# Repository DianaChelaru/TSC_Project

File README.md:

Acest proiect îmbină mai multe componente electronice conectate la un microcontroler ESP32-C6-WROOM-1-N8, creând o platformă embedded compactă destinată aplicațiilor cu senzoristică, comunicație wireless și o interfață de utilizator minimală. Platforma poate gestiona o serie de funcționalități, inclusiv monitorizarea și interacțiunea cu date în timp real, gestionarea energiei și stocarea datelor.

    Bill of Materials
|Componenta	|Link|	Datasheet|
|-----------|-----------------|---------------|
|112A-TAAR-R03_ATTEND |	https://store.comet.bg/en/Catalogue/Product/43497/ |	https://store.comet.bg/en/Catalogue/Product/43497/ |
|744043680IND_4828-WE-TPC_WRE |	https://www.digikey.sg/en/models/1638515 |	https://www.we-online.com/components/products/datasheet/744043680.pdf |
|ADAFRUIT_LEDCHIP-LED0603 |	https://www.snapeda.com/parts/KP-1608SURCK/Kingbright/view-part/?ref=search&t=LED%200603 |	https://www.snapeda.com/parts/KP-1608SURCK/Kingbright/datasheet/ |  
|SAMACSYS_PARTS_USB4110-GF-A|	https://componentsearchengine.com/part-view/USB4110-GF-A/GCT%20(GLOBAL%20CONNECTOR%20TECHNOLOGY) |	https://gct.co/files/drawings/usb4110.pdf |
|BD5229G-TR|	https://componentsearchengine.com/part-view/BD5229G-TR/ROHM%20Semiconductor |	https://datasheet.datasheetarchive.com/originals/distributors/Datasheets_SAMA/f2b9741ef86007909f138d561a359946.pdf |
|CPH3225A|	https://www.snapeda.com/parts/CPH3225A/Seiko+Instruments/view-part/?ref=eda |	https://www.snapeda.com/parts/CPH3225A/Seiko%20Instruments/datasheet/ |
|QWIIC_CONNECTORJS-1MM|	https://www.snapeda.com/parts/PRT-14417/SparkFun/view-part/ |	https://www.snapeda.com/parts/PRT-14417/SparkFun%20Electronics/datasheet/ |
|BUTTON_CUSYOMV1|	https://industry.panasonic.com/global/en/downloads?tab=cad&small_g_cd=203&part_no=EVQPUJ02K&q=RVZRUFVKMDJLJTdDMTMlN0MyMDMlN0MzNDU5JTdDMSU3QyU3QyU3Q2ZhbHNl	| https://industry.panasonic.com/global/en/downloads?tab=catalog&small_g_cd=203&part_no=EVQPUJ02K&q=RVZRUFVKMDJLJTdDMTMlN0MyMDMlN0MzNDU5JTdDMSU3QyU3QzIlN0NmYWxzZQ%3D%3D |
|ESP32_WROVER_EAGLE-LTSPICE_CC0402|	https://componentsearchengine.com/part-view/CC0402MRX5R5BB106/YAGEO |	https://componentsearchengine.com/Datasheets/2/CC0402MRX5R5BB106.pdf |
|CPH3225A|	https://www.snapeda.com/parts/CPH3225A/Seiko+Instruments/view-part/?ref=eda |	https://www.snapeda.com/parts/CPH3225A/Seiko%20Instruments/datasheet/ |
|DS3231SN|	https://www.snapeda.com/parts/DS3231SN%23/Analog+Devices/view-part/?ref=eda |	https://www.snapeda.com/parts/DS3231SN%23/Analog%20Devices/datasheet/ |
|ESP32_WROVER_EAGLE-LTSPICE_RR0402|	https://www.snapeda.com/parts/RC0402FR-07226RL/Yageo/view-part/	| https://www.snapeda.com/parts/RC0402FR-07226RL/Yageo/datasheet/ |
|ESP32_WROVER_BME680_BME680|	https://www.snapeda.com/parts/BME680/Bosch/view-part/?welcome=home |	https://www.snapeda.com/parts/BME680/Bosch%20Sensortec/datasheet/ |
|ESP32_WROVER_EAGLE-LTSPICE_CC0402|	https://componentsearchengine.com/Datasheets/2/CC0402MRX5R5BB106.pdf |	https://componentsearchengine.com/part-view/CC0402MRX5R5BB106/YAGEO |
|ESP32_WROVER_SPARKFUN-DISCRETESEMI_MOSFET_PCH-DMG2305UX-7|	https://componentsearchengine.com/part-view/DMG2305UX-7/Diodes%20Incorporated |	https://www.diodes.com//assets/Datasheets/DMG2305UX.pdf |
|ESP32C6_VARISTORCN1812|	https://www.mouser.co.uk/ProductDetail/EPCOS-TDK/B72520T0350K062?qs=dEfas%2FXlABIszF52uu7vrg%3D%3D	| https://www.tdk-electronics.tdk.com/inf/75/db/CTVS_14/Surge_protection_series.pdf |
|ESP32-C6-WROOM-1-N8| 	https://www.snapeda.com/parts/ESP32-C6-WROOM-1-N8/Espressif+Systems/view-part/?ref=eda |	https://www.snapeda.com/parts/ESP32-C6-WROOM-1-N8/Espressif%20Systems/datasheet/ |
|FH34SRJ-24S-0.5SH_99_ |	https://componentsearchengine.com/part-view/XC6220A331MR-G/Torex	| https://product.torexsemi.com/system/files/series/xc6220.pdf |
|MAX17048G+T10|	https://www.snapeda.com/parts/MAX17048G+T10/Analog+Devices/view-part/?ref=eda |	https://www.snapeda.com/parts/MAX17048G+T10/Analog%20Devices/datasheet/ |
|MBR0530|	https://ro.mouser.com/ProductDetail/KYOCERA-AVX/SD0805S020S1R0?qs=jCA%252BPfw4LHbpkAoSnwrdjw%3D%3D |	https://ro.mouser.com/datasheet/2/40/schottky-3165252.pdf |
|PGB1010603MR|	https://www.snapeda.com/parts/PGB1010603MR/Littelfuse/view-part/?ref=eda |	https://www.snapeda.com/parts/PGB1010603MR/Littelfuse%20Inc./datasheet/ |
|MCP73831 |	https://www.digikey.com/en/models/1874108 |	https://ww1.microchip.com/downloads/aemDocuments/documents/APID/ProductDocuments/DataSheets/MCP73831-Family-Data-Sheet-DS20001984H.pdf |
|RCL_CPOL-EUCT3528|	https://ro.mouser.com/ProductDetail/Vishay-Sprague/TR3B106K025C1300?qs=jCGqFXxTmLdffnuDkXzk1g%3D%3D |	https://www.vishay.com/docs/40080/tr3.pdf |
|SI1308EDL-T1-GE3|	https://componentsearchengine.com/part-view/SI1308EDL-T1-GE3/Vishay	| https://componentsearchengine.com/Datasheets/1/SI1308EDL-T1-GE3.pdf |
| SJ |	https://grabcad.com/library/solder-jumpers-1 | 
|USBLC6-2SC6Y |	https://www.snapeda.com/parts/USBLC6-2SC6Y/STMicroelectronics/view-part/?ref=eda	| https://www.snapeda.com/parts/USBLC6-2SC6Y/STMicroelectronics/datasheet/ |
|W25Q512JVEIQ|	https://www.snapeda.com/parts/W25Q512JVEIQ/Winbond+Electronics/view-part/?ref=eda |	https://www.snapeda.com/parts/W25Q512JVEIQ/Winbond%20Electronics/datasheet/ |
|XC6220A331MR-G|	https://componentsearchengine.com/part-view/XC6220A331MR-G/Torex |	https://product.torexsemi.com/system/files/series/xc6220.pdf|

    1. Microcontrolerul ESP32-C6-WROOM-1-N8
Descriere: Acesta este nucleul sistemului nostru și va gestiona toată logica și comunicațiile. Este un microcontroler cu suport pentru Wi-Fi și Bluetooth Low Energy (BLE), având o capacitate de procesare ridicată și multiple periferice integrate.

Componente hardware conectate:

Pinout: Conectarea senzorilor și modulelor va depinde de alegerea pinilor pe care i-am selectat pe ESP32, detaliată în documentație.

Interfețe: ESP32 folosește interfețe precum I2C, SPI și UART pentru a comunica cu componentele periferice.

    2. Senzori
Senzor de temperatură și umiditate (ex. DHT22):

Interfață: Digitală

Rol: Măsurarea temperaturii și umidității în mediu.

Comunicare: Acesta va comunica cu ESP32 folosind pinul GPIO (general-purpose input/output) pentru a obține valorile măsurate.

Senzor de lumină (ex. LDR):

Interfață: Analogică

Rol: Măsurarea intensității luminii din mediu.

Comunicare: Va fi conectat la un pin analogic al ESP32 pentru a permite citirea valorilor de lumină.

    3. RTC (Real-Time Clock)
Componente: Modul RTC (de exemplu, DS3231)

Interfață: I2C

Rol: Ținerea orei și datei, chiar și când microcontrolerul este alimentat cu baterie.

Comunicare: ESP32 se va conecta la RTC prin interfața I2C. Datele și ora vor fi extrase periodic din RTC pentru a menține sincronizarea corectă a sistemului.

    4. Memorie Externă
Componente: Modul de memorie flash (ex. SPI Flash)

Interfață: SPI

Rol: Stocarea datelor de configurare, date temporare, sau orice altă informație care trebuie păstrată între restarturi ale sistemului.

Comunicare: Memoria externă va comunica cu ESP32 prin interfața SPI, permițând citirea și scrierea rapidă a datelor.

    5. Alimentare și Managementul Energiei
Componente:

Regulator de tensiune: Acesta va asigura alimentarea stabilă a întregului sistem.

Baterie Li-Ion: O baterie de 3.7V va fi utilizată pentru a alimenta sistemul într-un mod eficient.

Consumul de Energie:

ESP32 este un microcontroler cu consum variabil, dar în mod normal consumă aproximativ 160 mA în mod activ și mult mai puțin în modul de adormire. Prin gestionarea corectă a modurilor de adormire, se poate reduce consumul total de energie la un nivel foarte scăzut.

Optimizare: Implementarea unui algoritm de gestionare a energiei va permite microcontrolerului să intre în moduri de adormire adâncă în timpul perioadelor de inactivitate, economisind astfel energie.

    6. Interfețe de Comunicație
Wi-Fi (IEEE 802.11b/g/n): ESP32 va fi capabil să comunice prin rețele Wi-Fi pentru a trimite date la servere sau pentru a se conecta la alte dispozitive.

Bluetooth Low Energy (BLE): Pentru comunicații cu alte dispozitive Bluetooth, cum ar fi smartphone-uri sau alte sisteme integrate.

    7. Protecții și Siguranță
Protecție la supratensiune și supracurent: Sistemul va include diode și rezistențe de protecție pentru a preveni daunele cauzate de condiții de tensiune necontrolată.

Siguranța bateriei: Managementul bateriei va include circuite de protecție pentru a preveni supraîncărcarea sau descărcarea excesivă.

    ⚡ Calcule de consum
Acestea sunt estimările de consum pentru fiecare componentă principală a platformei:

ESP32-C6 în modul activ: Aproximativ 80 mA.

Senzori activi (maxim): Între 10-20 mA.

În modul standby: Sub 10 mA, cu ESP în deep sleep și senzorii inactivi.

MCP73831 (încărcare): Până la 500 mA, în funcție de configurare.

Consum optimizat:

LDO XC6220A331MR-G, care este eficient la sarcini joase.

Mod de deep sleep al ESP32-C6 între măsurători.

Control MOSFET pentru a alimenta perifericele doar când este necesar.

    🔌 Pini folosiți pe ESP32-C6
Acestea sunt conexiunile pinilor ESP32-C6 la diversele componente ale proiectului:

|Pin ESP32-C6 |	Funcție	  |   Conectat la|
|-----------|--------------|-------------|  
|GPIO0   	  |  Buton USER	|    BUTTON_CUSTOMV1|
|GPIO1 (TX)  |	UART TX	     |   USB4110-GF-A|
|GPIO2 (RX)	 |   UART RX	  |      USB4110-GF-A|
|GPIO3	       | SDA I2C	  |      BME680, DS3231, MAX17048|
|GPIO4	      |  SCL I2C	  |      BME680, DS3231, MAX17048|
|GPIO5	       | SPI CS	      |  W25Q512JVEIQ|
|GPIO6	      |  SPI CLK	  |      W25Q512JVEIQ|
|GPIO7	      |  SPI MISO	  |  W25Q512JVEIQ|
|GPIO8	      |  SPI MOSI	  |  W25Q512JVEIQ|
|GPIO9	      |  LED	      |      ADAFRUIT_LEDCHIP-LED0603|
|GPIO10	      |  MOSFET control |	SI1308EDL-T1-GE3|

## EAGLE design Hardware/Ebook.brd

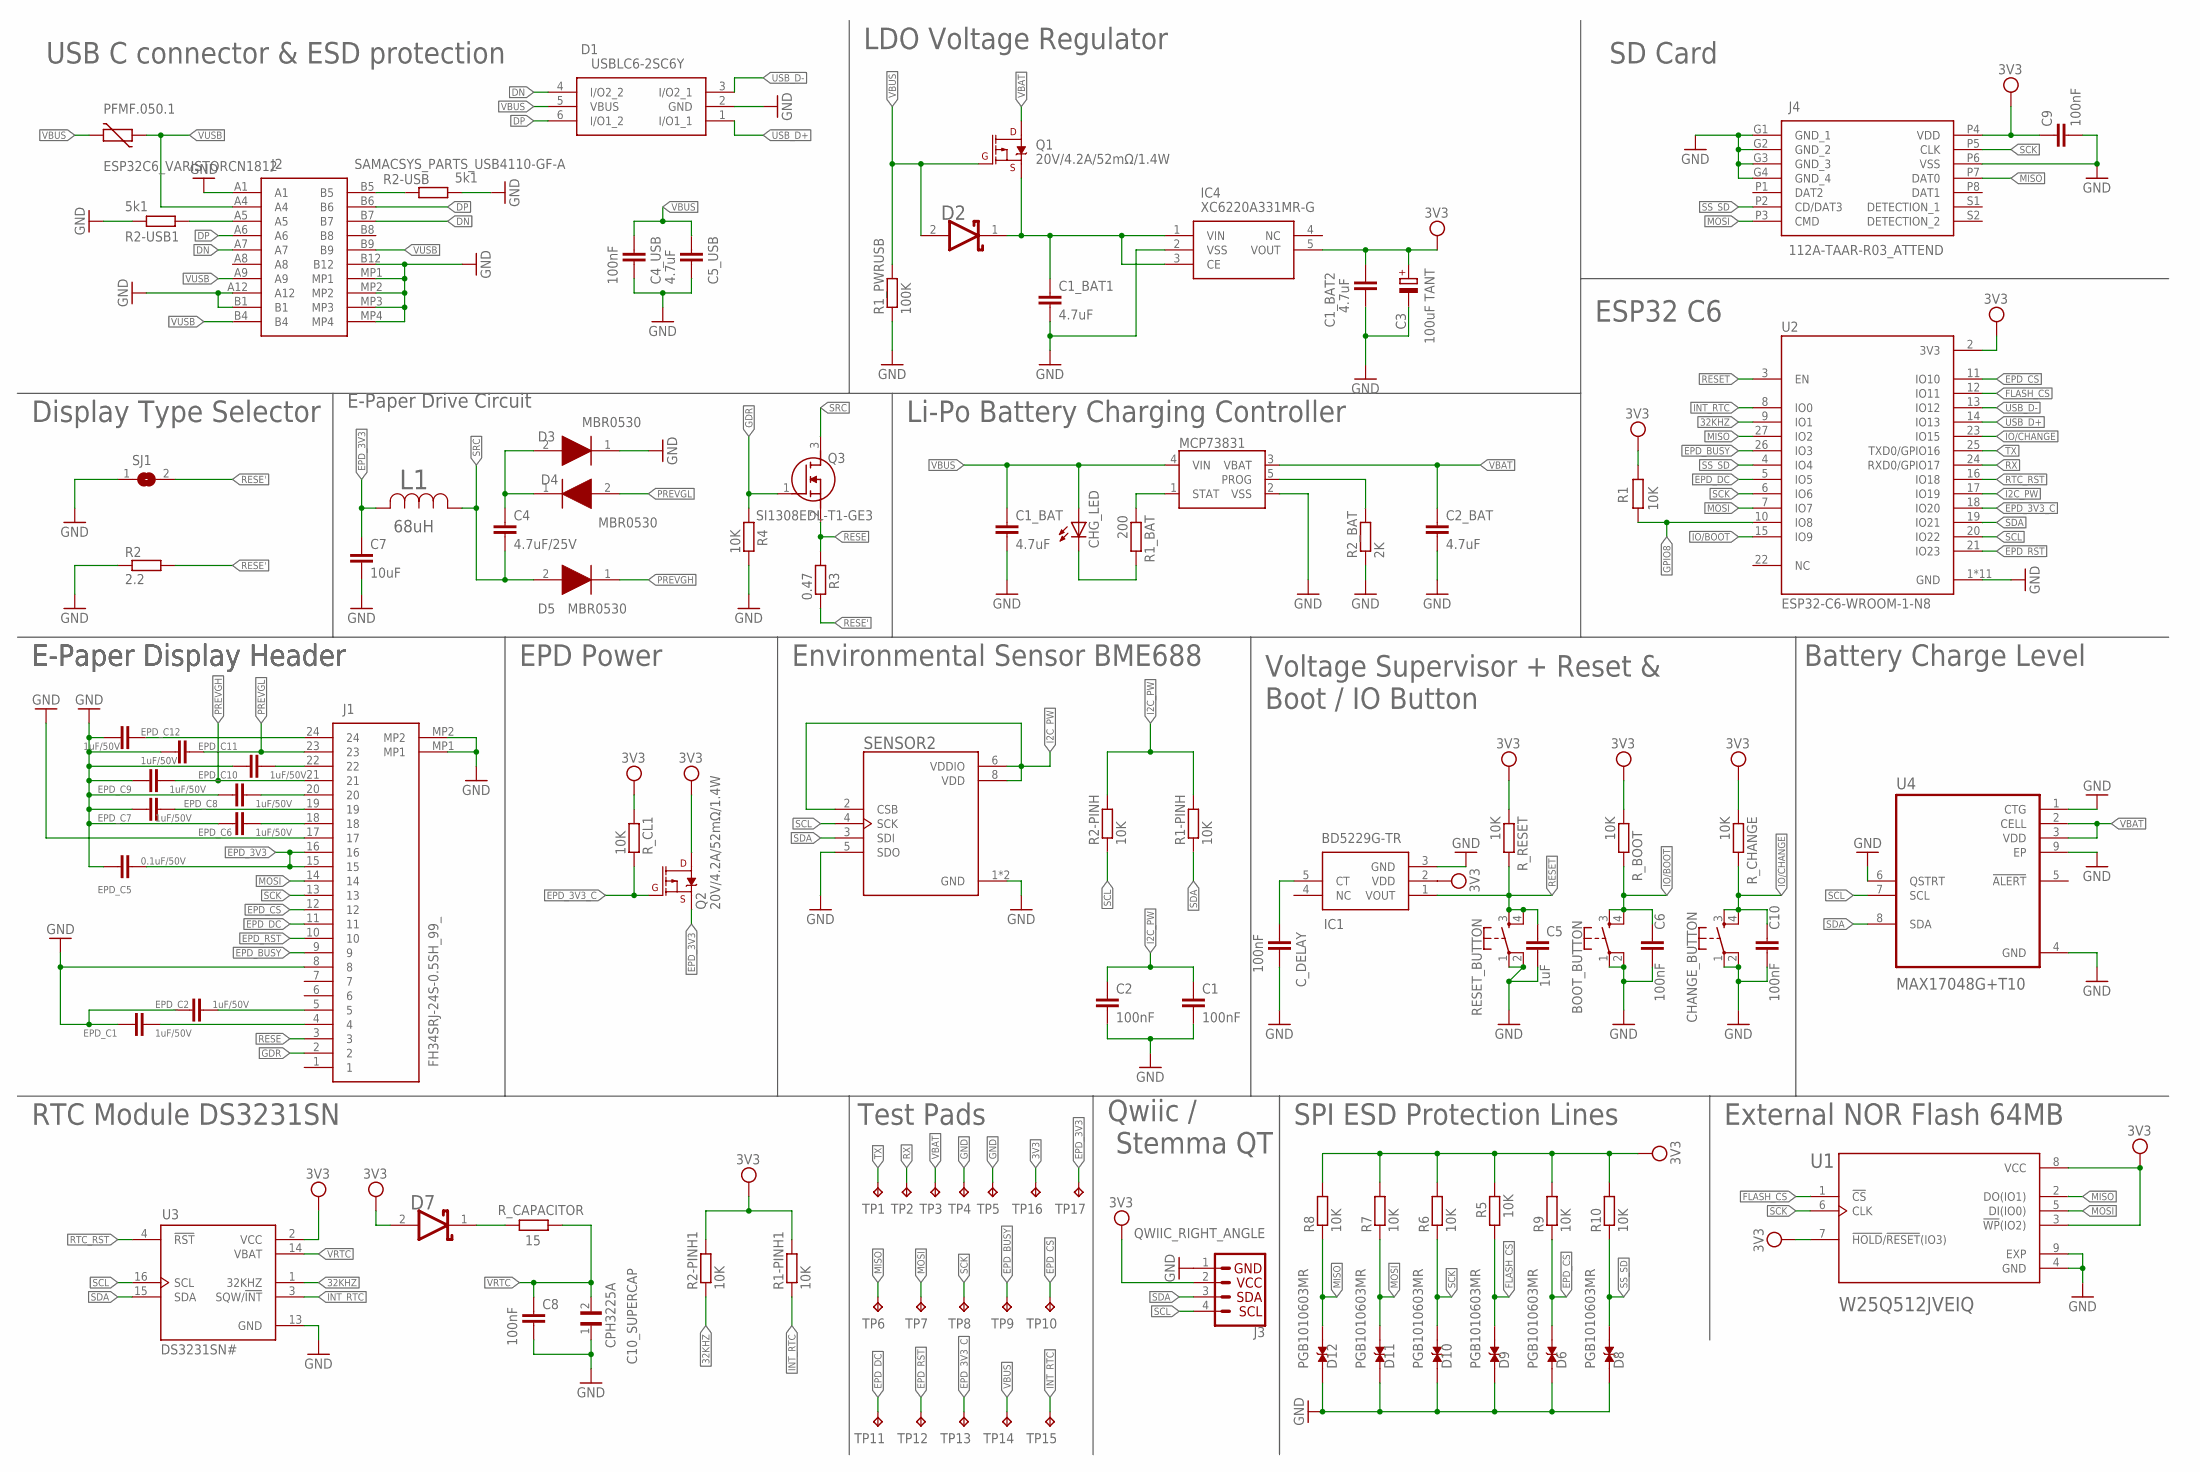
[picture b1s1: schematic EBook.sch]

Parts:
BOOT_BUTTON: BUTTON_CUSYOMV1; MYBUTTON
C1, C2, C4_USB, C6, C8, C9, C10: 100nF; EAGLE-LTSPICE_C0402
C1_BAT, C1_BAT1, C1_BAT2, C2_BAT, C5_USB: 4.7uF; EAGLE-LTSPICE_C0402
C3: 100uF TANT; RCL_CT3528
C4: 4.7uF/25V; EAGLE-LTSPICE_C0402
C5: 1uF; EAGLE-LTSPICE_C0402
C7: 10uF; EAGLE-LTSPICE_C0402
C10_SUPERCAP: CPH3225A; CAPCP3225X100N
CHANGE_BUTTON: BUTTON_CUSYOMV1; MYBUTTON
CHG_LED: ADAFRUIT_LEDCHIP-LED0603; ADAFRUIT_CHIP-LED0603
C_DELAY: 100nF; EAGLE-LTSPICE_C0402
D1: USBLC6-2SC6Y; SOT95P280X145-6N
D2, D7: ESP32_WROVER_AVX---SD0805S020S1R0_AVX_SD0805S020S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; ESP32_WROVER_AVX---SD0805S020S1R0_AVX_SD0805S020S1R0_0
D3, D4, D5: MBR0530; SOD3716X135N
D6, D8, D9, D10, D11, D12: PGB1010603MR; DIOC1608X36N
EPD_C1, EPD_C2, EPD_C6, EPD_C7, EPD_C8, EPD_C9, EPD_C10, EPD_C11, EPD_C12: 1uF/50V; EAGLE-LTSPICE_C0402
EPD_C5: 0.1uF/50V; EAGLE-LTSPICE_C0402
IC1: BD5229G-TR; SOT95P280X125-5N
IC4: XC6220A331MR-G; SOT95P280X120-5N
J1: FH34SRJ-24S-0.5SH_99_; FH34SRJ24S05SH99
J2: SAMACSYS_PARTS_USB4110-GF-A; SAMACSYS_PARTS_USB4110GFA
J3: QWIIC_RIGHT_ANGLE; JST04_1MM_RA
J4: 112A-TAAR-R03_ATTEND; 112ATAARR03ATTEND
L1: 68uH; IND_4828-WE-TPC_WRE
MCP73831: ESP32_WROVER_SPARKFUN-IC-POWER_MCP73831; ESP32_WROVER_SPARKFUN-IC-POWER_SOT23-5
PFMF.050.1: ESP32C6_VARISTORCN1812; ESP32C6_VARISTOR_CT/CN1812
Q1, Q2: 20V/4.2A/52mΩ/1.4W; ESP32_WROVER_SPARKFUN-DISCRETESEMI_SOT23-3
Q3: SI1308EDL-T1-GE3; SOT65P210X110-3N
R1, R1-PINH, R1-PINH1, R2-PINH, R2-PINH1, R4, R5, R6, R7, R8, R9, R10: 10K; ESP32_WROVER_EAGLE-LTSPICE_R0402
R1_BAT: 200; ESP32_WROVER_EAGLE-LTSPICE_R0402
R1_PWRUSB: 100K; ESP32_WROVER_EAGLE-LTSPICE_R0402
R2: 2.2; ESP32_WROVER_EAGLE-LTSPICE_R0402
R2-USB, R2-USB1: 5k1; ESP32_WROVER_EAGLE-LTSPICE_R0402
R2_BAT: 2K; ESP32_WROVER_EAGLE-LTSPICE_R0402
R3: 0.47; ESP32_WROVER_EAGLE-LTSPICE_R0402
RESET_BUTTON: BUTTON_CUSYOMV1; MYBUTTON
R_BOOT: 10K; ESP32_WROVER_EAGLE-LTSPICE_R0402
R_CAPACITOR: 15; ESP32_WROVER_EAGLE-LTSPICE_R0402
R_CHANGE: 10K; ESP32_WROVER_EAGLE-LTSPICE_R0402
R_CL1: 10K; ESP32_WROVER_EAGLE-LTSPICE_R0402
R_RESET: 10K; ESP32_WROVER_EAGLE-LTSPICE_R0402
SENSOR2: ESP32_WROVER_BME680_BME680; ESP32_WROVER_BME680_PSON80P300X300X100-8N
SJ1: SJ
TP1, TP2, TP3, TP4, TP5, TP6, TP7, TP8, TP9, TP10, TP11, TP12, TP13, TP14, TP15, TP16, TP17: TPTP20R; TP20R
U1: W25Q512JVEIQ; SON127P600X800X80-9N
U2: ESP32-C6-WROOM-1-N8; XCVR_ESP32-C6-WROOM-1-N8
U3: DS3231SN#; SOIC127P1032X265-16N
U4: MAX17048G+T10; SON50P200X200X80-9N

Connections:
3V3: C1_BAT2.1, C3.+, C9.1, D7.2 (ANODE), IC1.2 (VDD), IC4.5 (VOUT), J3.2, J4.P4 (VDD), Q2.3 (D), R1.1, R1-PINH1.2, R2-PINH1.2, R5.2, R6.2, R7.2, R8.2, R9.2, R10.2, R_BOOT.1, R_CHANGE.1, R_CL1.1, R_RESET.1, TP16.TP, U1.3 (!WP!(IO2)), U1.7 (!HOLD!/!RESET!(IO3)), U1.8 (VCC), U2.2 (3V3), U3.2 (VCC)
32KHZ: R2-PINH1.1, U2.9 (IO1), U3.1 (32KHZ)
DN: D1.4 (I/O2_2), J2.A7, J2.B7
DP: D1.6 (I/O1_2), J2.A6, J2.B6
EPD_3V3: C7.1, EPD_C5.1, J1.15, J1.16, L1.2, Q2.2 (S), TP17.TP
EPD_3V3_C: Q2.1 (G), R_CL1.2, TP13.TP, U2.18 (IO20)
EPD_BUSY: J1.9, TP9.TP, U2.26 (IO3)
EPD_CS: D6.2, J1.12, R9.1, TP10.TP, U2.11 (IO10)
EPD_DC: J1.11, TP11.TP, U2.5 (IO5)
EPD_RST: J1.10, TP12.TP, U2.21 (IO23)
FLASH_CS: D9.2, R5.1, U1.1 (!CS), U2.12 (IO11)
GDR: J1.2, Q3.1 (G), R4.1
GND: BOOT_BUTTON.1, BOOT_BUTTON.2, C1.2, C1_BAT.2, C1_BAT1.2, C1_BAT2.2, C2.2, C2_BAT.2, C3.-, C4_USB.2, C5.2, C5_USB.2, C6.2, C7.2, C8.2, C9.2, C10.2, C10_SUPERCAP.1, CHANGE_BUTTON.1, CHANGE_BUTTON.2, C_DELAY.2, D1.2 (GND), D3.1 (K), D6.1, D8.1, D9.1, D10.1, D11.1, D12.1, EPD_C1.2, EPD_C2.2, EPD_C5.2, EPD_C6.2, EPD_C7.2, EPD_C8.2, EPD_C9.2, EPD_C10.2, EPD_C11.2, EPD_C12.2, IC1.3 (GND), IC4.2 (VSS), J1.8, J1.17, J1.MP1, J1.MP2, J2.A1, J2.A12, J2.B1, J2.B12, J2.MP1, J2.MP2, J2.MP3, J2.MP4, J3.1, J4.G1 (GND_1), J4.G2 (GND_2), J4.G3 (GND_3), J4.G4 (GND_4), J4.P6 (VSS), MCP73831.2 (VSS), R1_PWRUSB.1, R2.1, R2-USB.2, R2-USB1.1, R2_BAT.1, R4.2, RESET_BUTTON.1, RESET_BUTTON.2, SENSOR2.1 (GND), SENSOR2.5 (SDO), SENSOR2.7 (GND), SJ1.1, TP4.TP, TP5.TP, U1.4 (GND), U1.9 (EXP), U2.1 (GND), U2.28 (GND), U2.29_1 (GND), U2.29_2 (GND), U2.29_3 (GND), U2.29_4 (GND), U2.29_5 (GND), U2.29_6 (GND), U2.29_7 (GND), U2.29_8 (GND), U2.29_9 (GND), U3.13 (GND), U4.1 (CTG), U4.4 (GND), U4.6 (QSTRT), U4.9 (EP)
GPIO8: R1.2, U2.10 (IO8)
I2C_PW: C1.1, C2.1, R1-PINH.2, R2-PINH.2, SENSOR2.2 (CSB), SENSOR2.6 (VDDIO), SENSOR2.8 (VDD), U2.17 (IO19)
INT_RTC: R1-PINH1.1, TP15.TP, U2.8 (IO0), U3.3 (SQW/!INT)
IO/BOOT: BOOT_BUTTON.3, BOOT_BUTTON.4, C6.1, R_BOOT.2, U2.15 (IO9)
IO/CHANGE: C10.1, CHANGE_BUTTON.3, CHANGE_BUTTON.4, R_CHANGE.2, U2.23 (IO15)
MISO: D12.2, J4.P7 (DAT0), R8.1, TP6.TP, U1.2 (DO(IO1)), U2.27 (IO2)
MOSI: D11.2, J1.14, J4.P3 (CMD), R7.1, TP7.TP, U1.5 (DI(IO0)), U2.7 (IO7)
unnamed: J2.B5, R2-USB.1
unnamed: EPD_C6.1, J1.18
unnamed: J2.A5, R2-USB1.2
unnamed: C1_BAT1.1, D2.1 (CATHODE), IC4.1 (VIN), IC4.3 (CE), Q1.2 (S)
unnamed: C4.1, D3.2 (A), D4.1 (K)
unnamed: EPD_C7.1, J1.19
unnamed: MCP73831.5 (PROG), R2_BAT.2
unnamed: MCP73831.1 (STAT), R1_BAT.1
unnamed: CHG_LED.C, R1_BAT.2
unnamed: C_DELAY.1, IC1.5 (CT)
unnamed: EPD_C10.1, J1.22
unnamed: EPD_C2.1, J1.5
unnamed: D7.1 (CATHODE), R_CAPACITOR.2
unnamed: EPD_C12.1, J1.24
unnamed: EPD_C8.1, J1.20
unnamed: EPD_C1.1, J1.4
PREVGH: D5.1 (K), EPD_C9.1, J1.21
PREVGL: D4.2 (A), EPD_C11.1, J1.23
RESE: J1.3, Q3.2 (S), R3.1
RESE': R2.2, R3.2, SJ1.2
RESET: C5.1, IC1.1 (VOUT), RESET_BUTTON.3, RESET_BUTTON.4, R_RESET.2, U2.3 (EN)
RTC_RST: U2.16 (IO18), U3.4 (!RST)
RX: TP2.TP, U2.24 (RXD0/GPIO17)
SCK: D10.2, J1.13, J4.P5 (CLK), R6.1, TP8.TP, U1.6 (CLK), U2.6 (IO6)
SCL: J3.4, R2-PINH.1, SENSOR2.4 (SCK), U2.20 (IO22), U3.16 (SCL), U4.7 (SCL)
SDA: J3.3, R1-PINH.1, SENSOR2.3 (SDI), U2.19 (IO21), U3.15 (SDA), U4.8 (SDA)
SRC: C4.2, D5.2 (A), L1.1, Q3.3 (D)
SS_SD: D8.2, J4.P2 (CD/DAT3), R10.1, U2.4 (IO4)
TX: TP1.TP, U2.25 (TXD0/GPIO16)
USB_D+: D1.1 (I/O1_1), U2.14 (IO13)
USB_D-: D1.3 (I/O2_1), U2.13 (IO12)
VBAT: C2_BAT.1, MCP73831.3 (VBAT), Q1.3 (D), TP3.TP, U4.2 (CELL), U4.3 (VDD)
VBUS: C1_BAT.1, C4_USB.1, C5_USB.1, CHG_LED.A, D1.5 (VBUS), D2.2 (ANODE), MCP73831.4 (VIN), PFMF.050.1.2, Q1.1 (G), R1_PWRUSB.2, TP14.TP
VRTC: C8.1, C10_SUPERCAP.2, R_CAPACITOR.1, U3.14 (VBAT)
VUSB: J2.A4, J2.A9, J2.B4, J2.B9, PFMF.050.1.1

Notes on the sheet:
USB C connector & ESD protection
LDO Voltage Regulator
SD Card
ESP32 C6
Li-Po Battery Charging Controller
E-Paper Drive Circuit
Display Type Selector
E-Paper Display Header
EPD Power
Environmental Sensor BME688
Voltage Supervisor + Reset & Boot / IO Button
Battery Charge Level
RTC Module DS3231SN
Test Pads
Qwiic / Stemma QT
SPI ESD Protection Lines
External NOR Flash 64MB

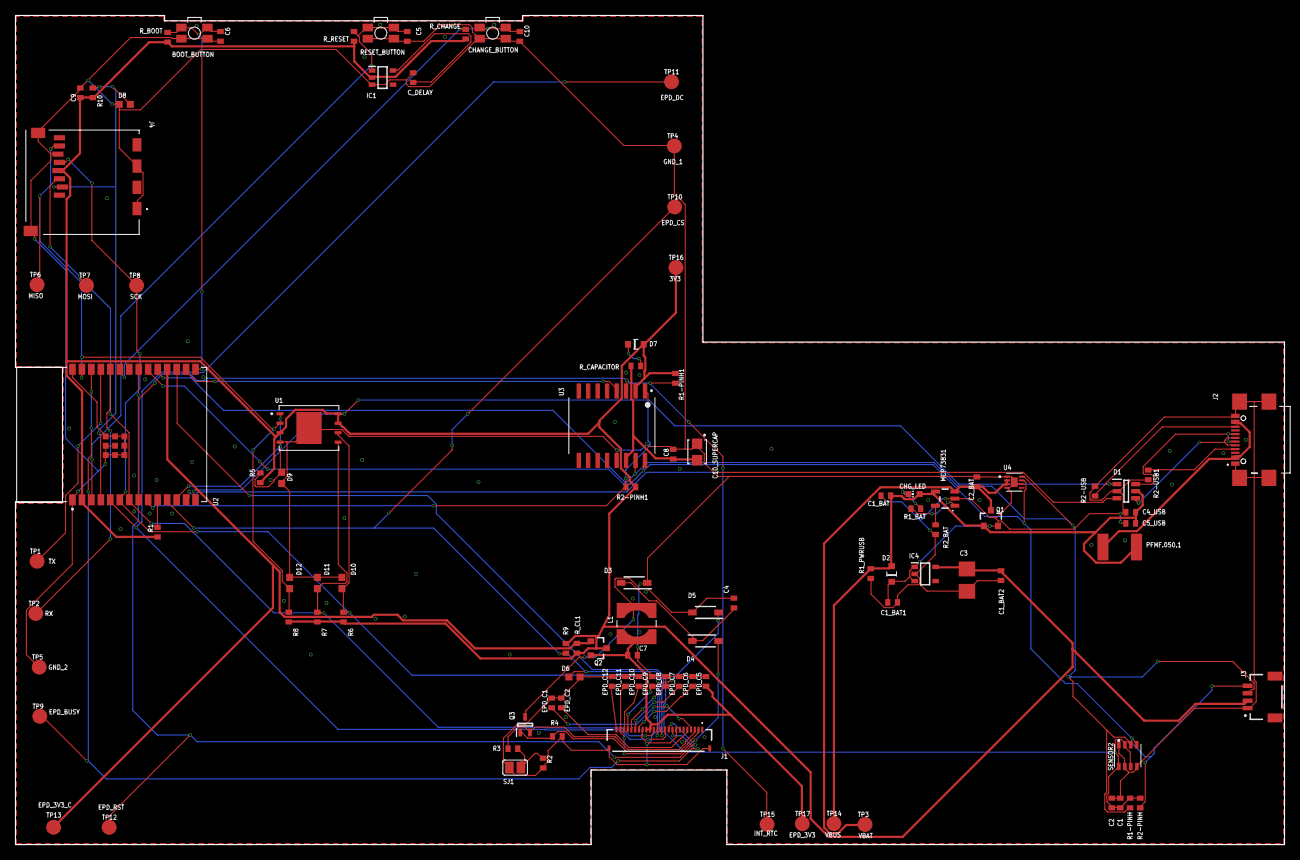
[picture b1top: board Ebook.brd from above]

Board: 2 copper layers, 170.2 x 111.2 mm, 103 parts (0 on the bottom side), 55 nets.

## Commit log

2025-04-06 Create Hardware

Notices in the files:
parts and their libraries:
DeskAssistant v19 v1: COPYRIGHT: Copyright (C) 2024 Ultra Librarian. All rights reserved.
